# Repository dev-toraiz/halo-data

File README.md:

# Halo Drone - ESP32 Flight Controller Project

ESP32ベースのクアッドコプター用フライトコントローラープロジェクト

## プロジェクト構成

```
halo-data/
├── halo-flight-controller/    # メインのフライトコントローラー
├── archives/                   # 過去のバージョン・参考実装
├── test-tools/                 # ハードウェアテストツール
├── development/                # 開発環境・実験コード
└── docs/                       # ドキュメント・回路図
```

## メインフライトコントローラー

### [halo-flight-controller/](halo-flight-controller/)

現在の最新実装。以下の2つのバージョンがあります：

#### h.ino
- **IMU**: MPU6050（ライブラリ使用）
- **姿勢推定**: Madgwickフィルター（6DOF）
- **受信機**: PPM（6チャネル）
- **モーターピン**: 16, 17, 18, 19
- **PWM方式**: ledcAttach（ESP32 Arduino Core 3.x対応）
- **PID制御**: 角度モード（2段階PID）
  - Angle PID: Roll/Pitch (P=6.06, I=0, D=0.83)
  - Yaw: レートモード (P=0, I=0, D=0)
- **特徴**: モーター個別オフセット、フレームレート計測

#### halo_contoroller_241201.ino
- ESCキャリブレーション機能付き
- その他の仕様は h.ino と同じ

### 主な機能
- MPU6050によるIMU読み取り
- Madgwickフィルタによる姿勢推定
- PPM受信機からの制御信号受信
- PID制御によるクアッドコプター安定化
- 4モーター独立制御

## アーカイブ

### [archives/](archives/)

#### ESP32-Flight-controller-main/
オリジナルの実装。Kalmanフィルター使用、8チャネルPPM対応。

主なファイル:
- `Anglemode_flightcontroller_ver3/` - メインのフライトコントローラー
- `motor_calibration_esp32/` - モーターキャリブレーション
- `reciever_pwm_esp32/` - 受信機テスト
- `measure_angles_from_mpu/` - IMU角度測定
- `Voltage_measurement_esp32/` - バッテリー電圧測定
- `anglemode_flightcontroller_ver3_PID_values_tuning_webserver/` - Webサーバー経由PIDチューニング

#### halo_contoroller/
旧バージョンの実装

#### esp-drone-master/
Espressif公式のドローン参考実装

## テストツール

### [test-tools/](test-tools/)

ハードウェアの動作確認用ツール:
- **ESC_Checker/** - ESC（モータードライバー）チェック
- **L293D_Checker/** - L293Dモータードライバーチェック
- **MPU6050_Checker/** - MPU6050 IMUセンサーチェック
- **PPM_Checker/** - PPM受信機チェック
- **ppm_receiver/** - PPM受信機テスト

## 開発環境

### [development/](development/)

開発関連ファイル:
- **PlatFormIO/** - PlatformIO プロジェクト
- **ArduinoIDE/** - Arduino IDE プロジェクト
- **Python/** - Pythonスクリプト
- **MINI-python/** - 小規模Pythonツール
- **filters/** - フィルター実験コード
- **controller/** - コントローラー関連
- **h/** - h.inoのオリジナルディレクトリ
- **halo_contoroller_241201/** - 最新版のオリジナルディレクトリ

## ドキュメント

### [docs/](docs/)

- **Circuit/** - 回路図・基板設計
  - `micon_board/` - マイコンボード設計
- **その他関連データ/** - その他のドキュメント

## ハードウェア仕様

### 主要コンポーネント
- **マイコン**: ESP32
- **IMU**: MPU6050（加速度計 + ジャイロ）
- **モーター**: 4基（ブラシレスモーター）
- **ESC**: 各モーター用に1基ずつ
- **受信機**: PPM方式（6チャネル）

### ピン配置（halo-flight-controller）
- **PPM入力**: GPIO 4
- **モーター1**: GPIO 16 (Front Left)
- **モーター2**: GPIO 17 (Front Right)
- **モーター3**: GPIO 18 (Back Right)
- **モーター4**: GPIO 19 (Back Left)
- **I2C (MPU6050)**: SDA/SCL（デフォルト）

### モーター配置（X型クアッド）
```
    Front
  M1     M2
    \ X /
    / X \
  M4     M3
    Rear
```

## セットアップ

### 必要なライブラリ
- Wire (標準)
- MadgwickAHRS
- MPU6050
- Arduino (ESP32 Core)

### 初回セットアップ
1. ESP32ボードを水平な場所に設置
2. コードをアップロード
3. キャリブレーション待機（約10秒）
4. LED点滅後、飛行準備完了

### ESCキャリブレーション（必要に応じて）
`halo_contoroller_241201.ino`の`calibrateESCs()`関数を有効化してアップロード

## PIDチューニング

### 現在の設定値
- **Angle PID (Roll/Pitch)**
  - P: 6.06
  - I: 0.00
  - D: 0.83
- **Angle Limits**
  - Max Roll: 18度
  - Max Pitch: 18度
  - Max Yaw Rate: 10度/秒

### チューニング方法
1. コード内のPIDパラメータを調整
2. 再アップロード
3. または、WebサーバーPIDチューニング版を使用（archives/ESP32-Flight-controller-main/参照）

## 安全上の注意

1. **初回テストは必ず屋外で実施**
2. **プロペラの回転方向を回路図通りに確認**
3. **モーター回転方向をメインコードアップロード前に確認**
4. **バッテリー電圧を定期的にチェック**
5. **テスト時はプロペラガードの使用を推奨**

## トラブルシューティング

### MPU6050接続失敗
- I2C配線を確認
- MPU6050の電源供給を確認
- I2Cプルアップ抵抗（4.7kΩ）の確認

### モーターが回転しない
- ESCキャリブレーションを実行
- モーターピン配線を確認
- スロットル最小値以上であることを確認

### 機体が不安定
- PIDパラメータを調整
- センサーキャリブレーションをやり直す
- モーターバランスを確認

## ライセンス

各サブプロジェクトのライセンスに従います。

## 参考リンク

- ESP32 Flight Controller YouTube: https://youtu.be/BcPTe-hTJGc
- Tutorial Video: https://www.youtube.com/watch?v=TmAVuMhu9no

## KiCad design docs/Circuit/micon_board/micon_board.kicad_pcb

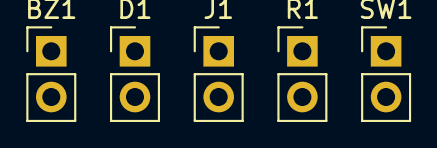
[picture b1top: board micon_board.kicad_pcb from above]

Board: 2 copper layers, 9 parts (0 on the bottom side), 4 nets, no tracks yet.

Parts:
BZ1: Buzzer; PinHeader_1x02_P2.54mm_Vertical
D1: LED; PinHeader_1x02_P2.54mm_Vertical
H1, H2, H3, H4: MountingHole; MountingHole_3.2mm_M3
J1: Conn_01x02_Pin; PinHeader_1x02_P2.54mm_Vertical
R1: R; PinHeader_1x02_P2.54mm_Vertical
SW1: SW_DPST_x2; PinHeader_1x02_P2.54mm_Vertical

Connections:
unnamed: BZ1.1 (+), D1.2 (A), SW1.2 (B)
unnamed: BZ1.2 (-), J1.1, R1.1
unnamed: D1.1 (K), R1.2
unnamed: J1.2, SW1.1 (A)

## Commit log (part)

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2024-12-14 [Add]
2024-12-15 [Change]
2024-12-28 [Add]PPM Checker
2025-01-26 [Chnage]
